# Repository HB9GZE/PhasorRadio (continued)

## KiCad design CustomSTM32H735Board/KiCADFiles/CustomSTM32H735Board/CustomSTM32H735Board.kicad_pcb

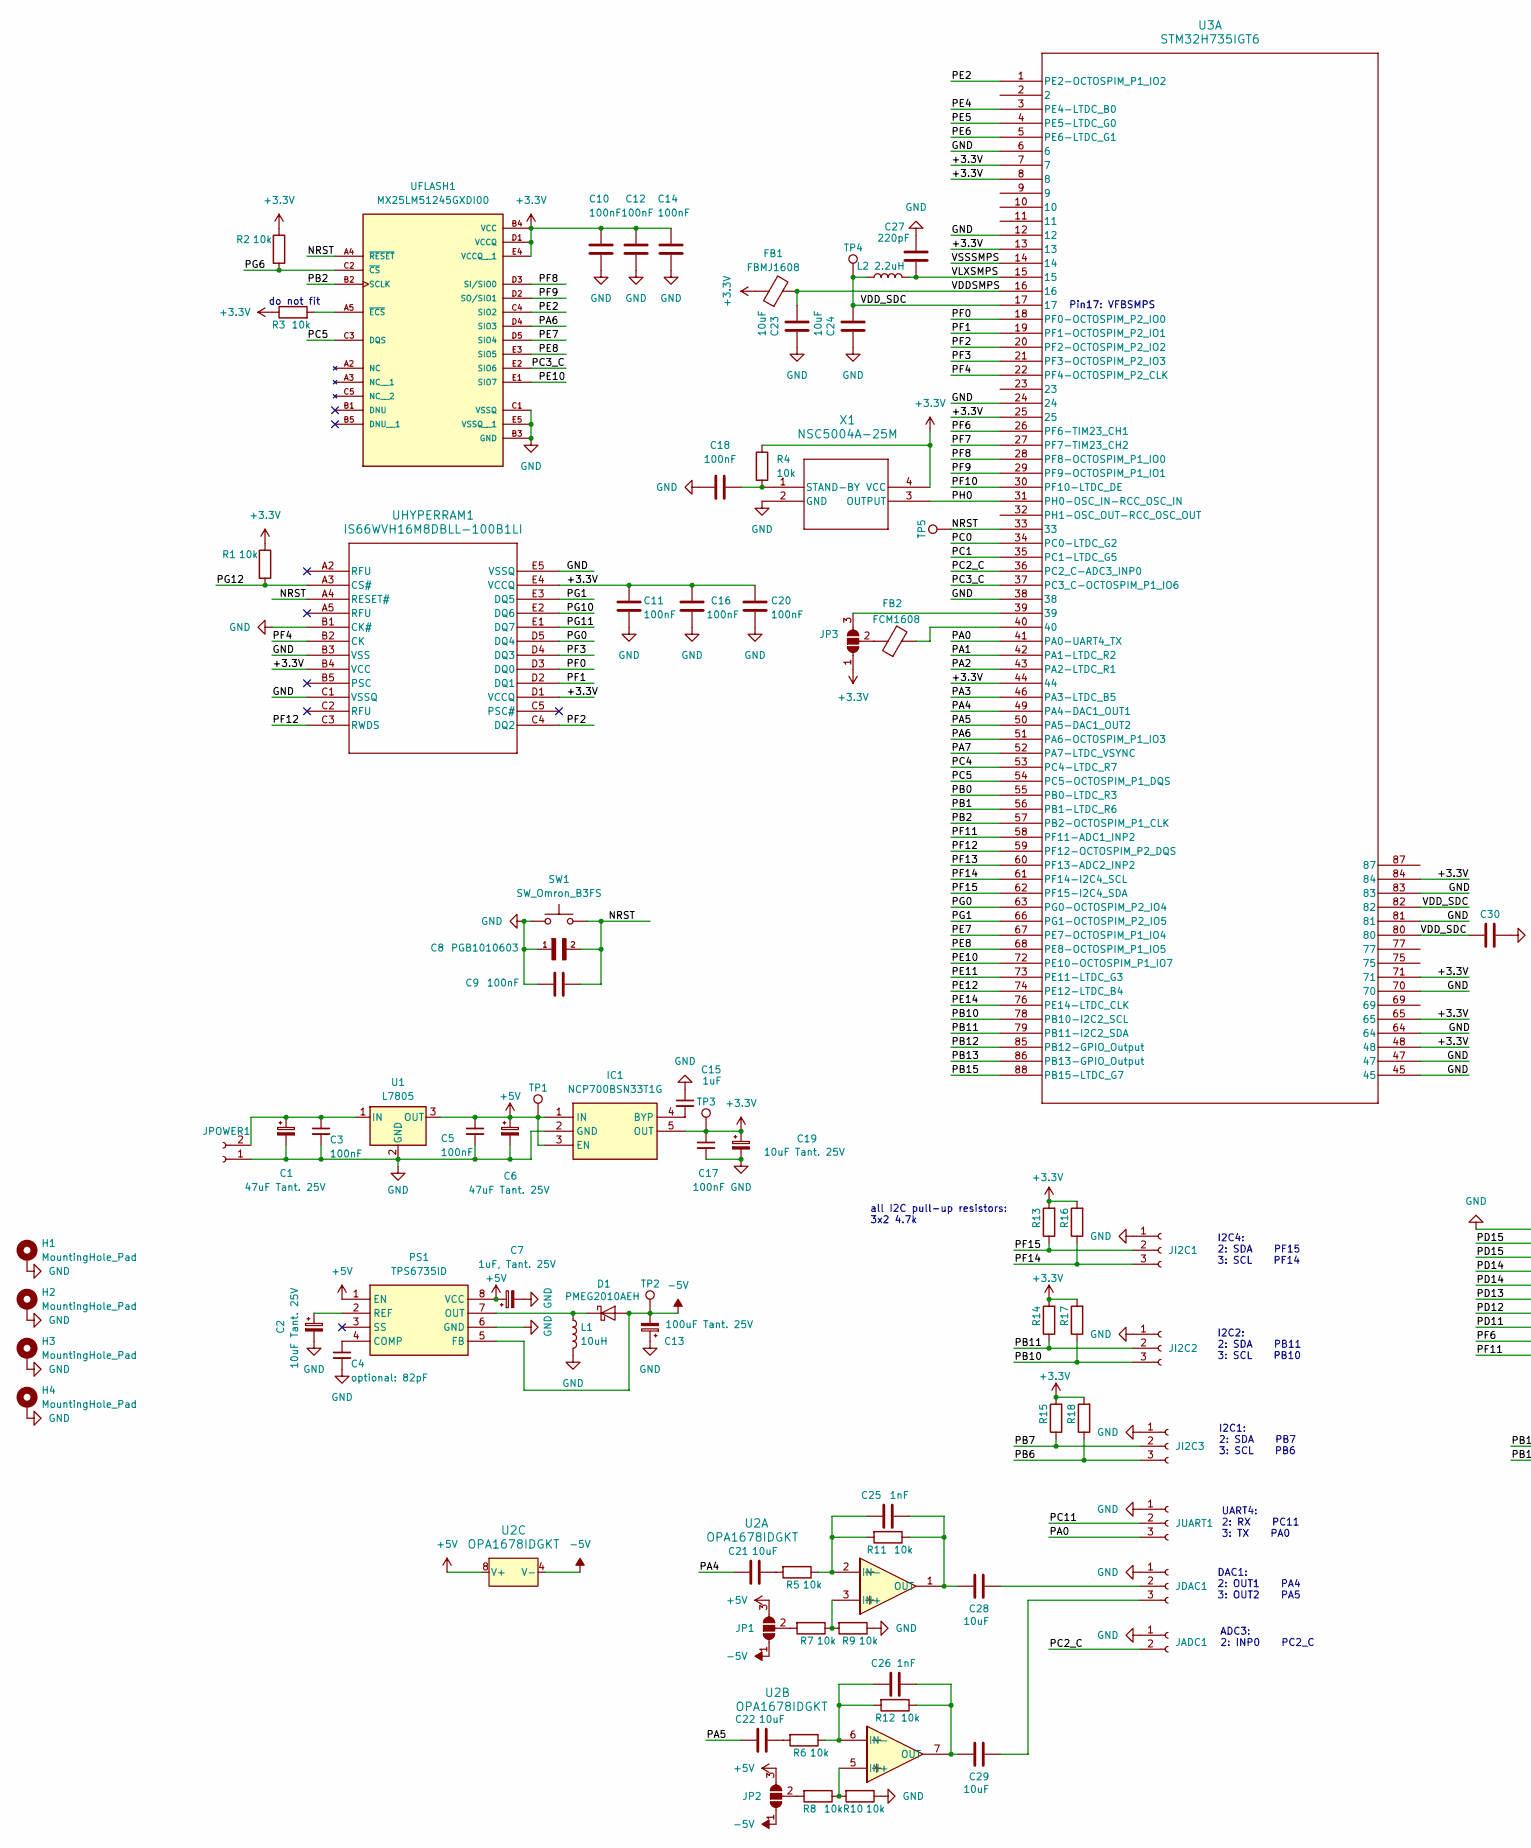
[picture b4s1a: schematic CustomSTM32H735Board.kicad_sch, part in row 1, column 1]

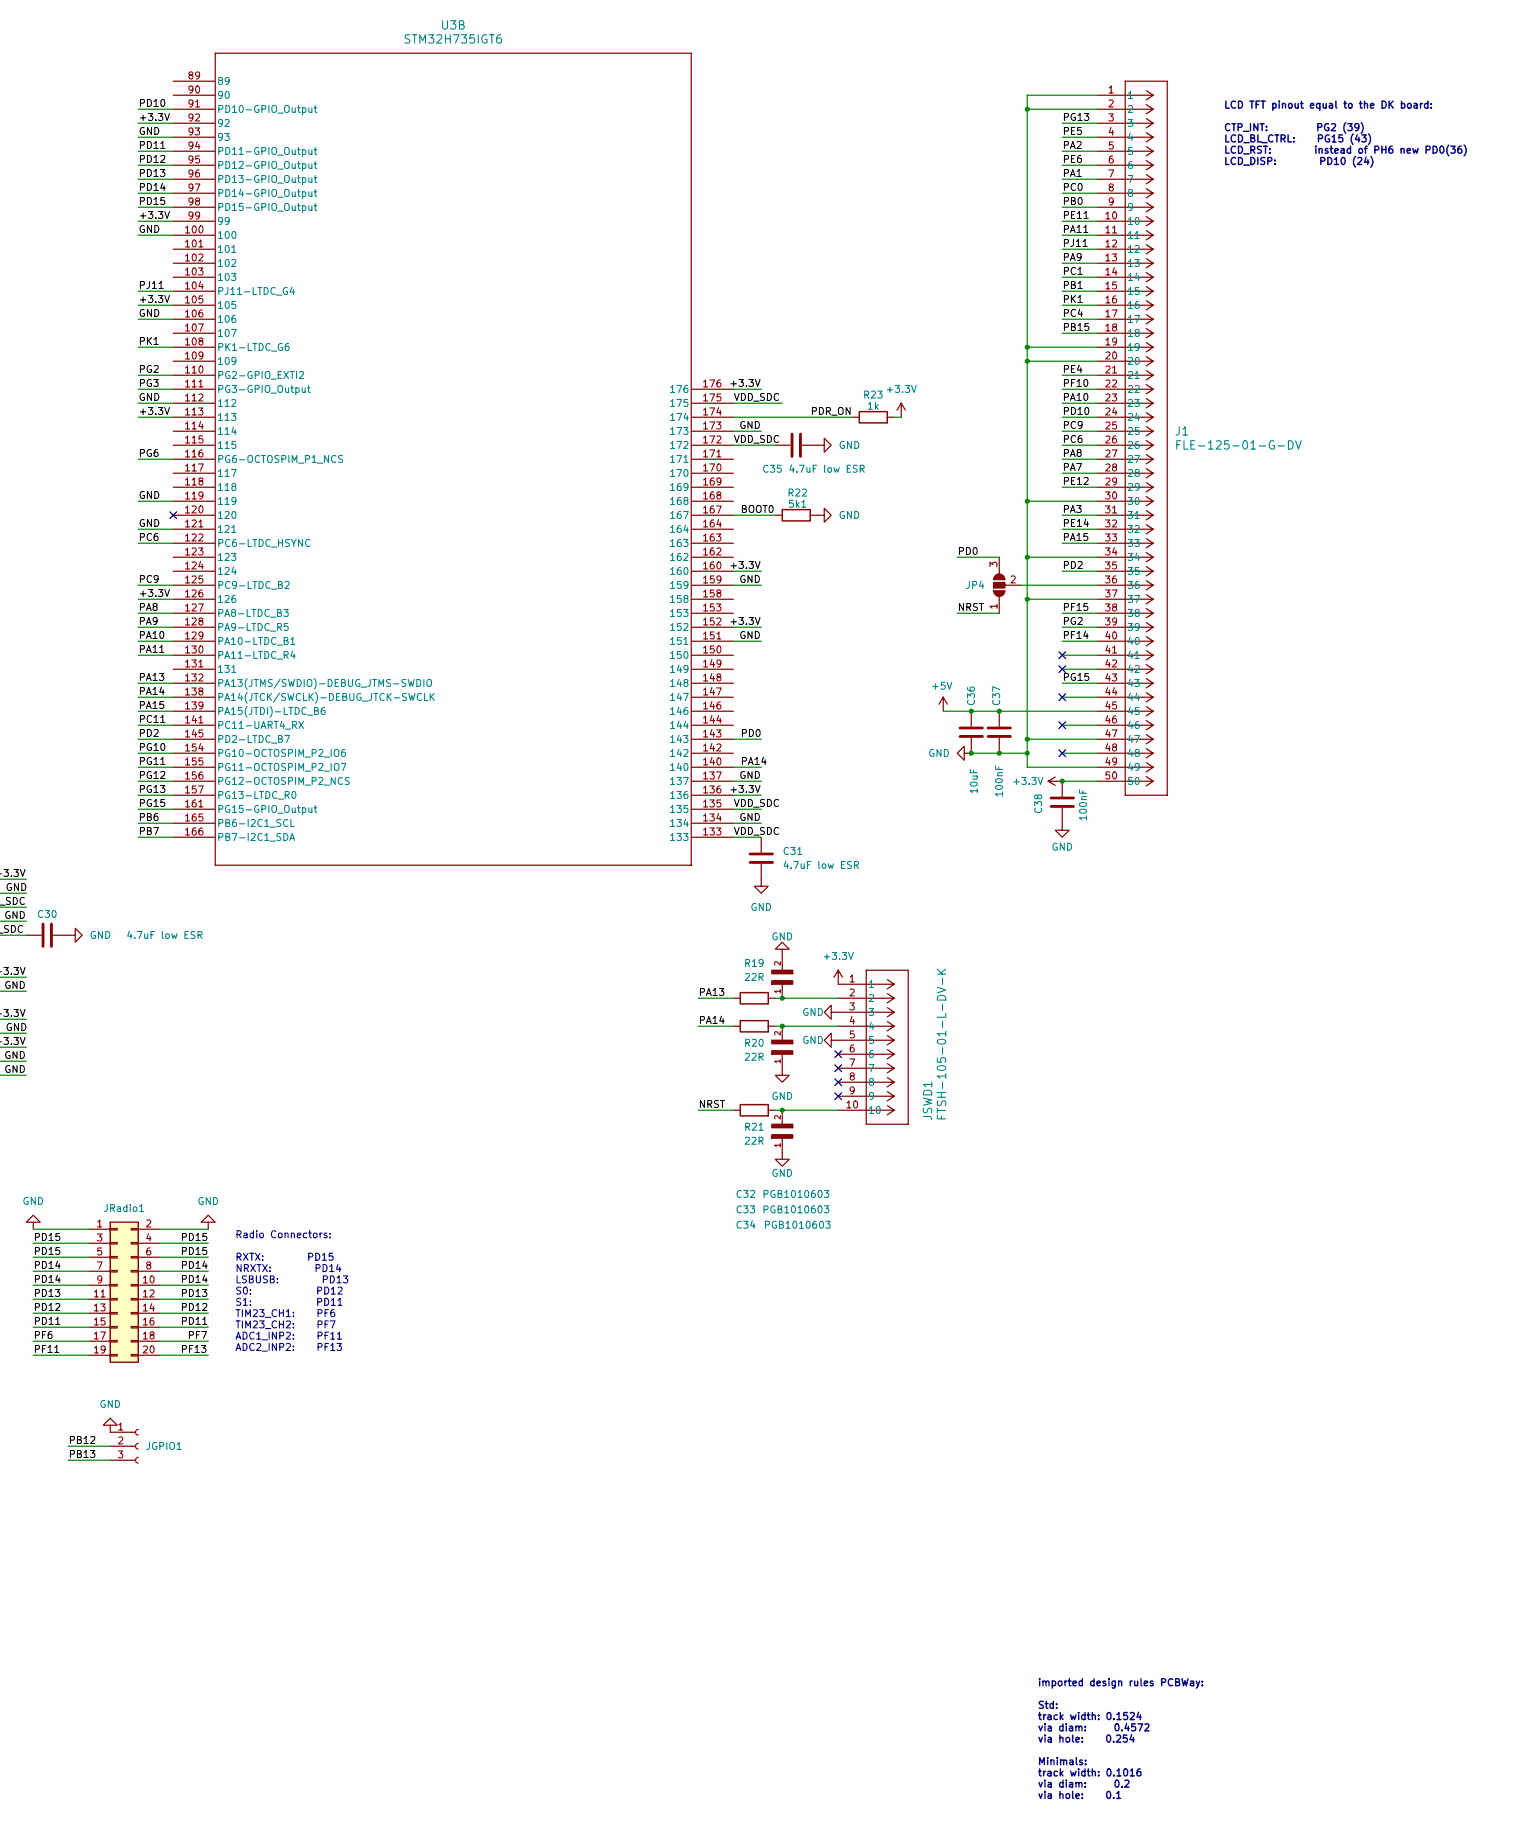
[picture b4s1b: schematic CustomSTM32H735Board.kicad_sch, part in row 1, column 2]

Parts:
C1, C6: 47uF Tant. 25V; CP_EIA-7343-30_AVX-N_Pad2.25x2.55mm_HandSolder
C2, C19: 10uF Tant. 25V; CP_EIA-7343-30_AVX-N_Pad2.25x2.55mm_HandSolder
C3, C5, C9, C10, C11, C12, C14, C16, C17, C18, C20, C37, C38: 100nF; C_0805_2012Metric_Pad1.18x1.45mm_HandSolder
C4: optional: 82pF; C_0805_2012Metric_Pad1.18x1.45mm_HandSolder
C7: 1uF, Tant. 25V; CP_EIA-7343-30_AVX-N_Pad2.25x2.55mm_HandSolder
C8, C32, C33, C34: PGB1010603; C_0603_1608Metric
C13: 100uF Tant. 25V; CP_EIA-7343-30_AVX-N_Pad2.25x2.55mm_HandSolder
C15: 1uF; C_0805_2012Metric_Pad1.18x1.45mm_HandSolder
C21, C22, C23, C24, C28, C29, C36: 10uF; C_0805_2012Metric_Pad1.18x1.45mm_HandSolder
C25, C26: 1nF; C_0805_2012Metric_Pad1.18x1.45mm_HandSolder
C27: 220pF; C_0805_2012Metric_Pad1.18x1.45mm_HandSolder
C30, C31, C35: 4.7uF low ESR; C_0805_2012Metric_Pad1.18x1.45mm_HandSolder
D1: PMEG2010AEH; D_SOD-123F
FB1: FBMJ1608; L_0603_1608Metric_Pad1.05x0.95mm_HandSolder
FB2: FCM1608; L_0603_1608Metric_Pad1.05x0.95mm_HandSolder
H1, H2, H3, H4: MountingHole_Pad; MountingHole_3.2mm_M3_Pad_TopBottom
IC1: NCP700BSN33T1G; SOT95P275X120-5N; Manufacturer_Part_Number NCP700BSN33T1G; Mouser Part Number 863-NCP700BSN33T1G
J1: FLE-125-01-G-DV; CON50_2X25_UF_FLE_SAI
JADC1: Conn_01x02_Socket; JST_XH_B2B-XH-A_1x02_P2.50mm_Vertical
JDAC1: Conn_01x03_Socket; JST_XH_B3B-XH-A_1x03_P2.50mm_Vertical
JGPIO1: Conn_01x03_Socket; JST_XH_B3B-XH-A_1x03_P2.50mm_Vertical
JI2C1, JI2C2, JI2C3: Conn_01x03_Socket; JST_XH_B3B-XH-A_1x03_P2.50mm_Vertical
JP1, JP2, JP3, JP4: SolderJumper_3_Open; SolderJumper-3_P1.3mm_Open_Pad1.0x1.5mm_NumberLabels
JPOWER1: Conn_01x02_Socket; JST_XH_B2B-XH-A_1x02_P2.50mm_Vertical
JRadio1: Conn_02x10_Odd_Even; IDC-Header_2x10_P2.54mm_Vertical
JSWD1: FTSH-105-01-L-DV-K; CON10_2X5_DUK_FTSH_SAI-M
JUART1: Conn_01x03_Socket; JST_XH_B3B-XH-A_1x03_P2.50mm_Vertical
L1: 10uH; L_1812_4532Metric_Pad1.30x3.40mm_HandSolder
L2: 2.2uH; L_Murata_DFE201610P
PS1: TPS6735ID; SOIC127P600X175-8N; Manufacturer_Part_Number TPS6735ID; Mouser Part Number 595-TPS6735ID
R1, R2, R3, R4, R5, R6, R7, R8, R9, R10, R11, R12: 10k; R_0805_2012Metric_Pad1.20x1.40mm_HandSolder
R13, R14, R15, R16, R17, R18: 4.7k; R_0805_2012Metric_Pad1.20x1.40mm_HandSolder
R19, R20, R21: 22R; R_0805_2012Metric_Pad1.20x1.40mm_HandSolder
R22: 5k1; R_0805_2012Metric_Pad1.20x1.40mm_HandSolder
R23: 1k; R_0805_2012Metric_Pad1.20x1.40mm_HandSolder
SW1: SW_Omron_B3FS; SW_SPST_Omron_B3FS-100xP
TP1, TP2, TP3, TP4, TP5: TestPoint; Pin_D0.7mm_L6.5mm_W1.8mm_FlatFork
U1: L7805; TO-220-3_Horizontal_TabDown
U2: OPA1678IDGKT; OPA1678_L
U3: STM32H735IGT6; LQFP176_STM32H735IGT6_STM-M
UFLASH1: MX25LM51245GXDI00; BGA24C100P5X5_600X800X120; PARTREV 1.1
UHYPERRAM1: IS66WVH16M8DBLL-100B1LI; TFBGA24_6X8_ISI
X1: NSC5004A-25M; NSC5004_NDK

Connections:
+3.3V: C10.1, C11.1, C12.1, C14.1, C16.1, C17.1, C19.1, C20.1, C38.1, FB1.1, IC1.5 (OUT), J1.50, JP3.1 (A), JSWD1.1, R1.1, R2.1, R3.1, R4.1, R13.2, R14.2, R15.2, R16.2, R17.2, R18.2, R23.2, TP3.1, U3.7, U3.8, U3.13, U3.25, U3.44, U3.48, U3.65, U3.71, U3.84, U3.92, U3.99, U3.105, U3.113, U3.126, U3.136, U3.152, U3.160, U3.176, UFLASH1.B4 (VCC), UFLASH1.D1 (VCCQ), UFLASH1.E4 (VCCQ__1), UHYPERRAM1.B4 (VCC), UHYPERRAM1.D1 (VCCQ), UHYPERRAM1.E4 (VCCQ), X1.4 (VCC)
+5V: C5.1, C6.1, C7.1, C36.1, C37.1, IC1.1 (IN), IC1.3 (EN), J1.45, JP1.3 (B), JP2.3 (B), PS1.1 (EN), PS1.8 (VCC), TP1.1, U1.3 (OUT), U2.8 (V+)
-5V: C13.2, D1.2 (A), JP1.1 (A), JP2.1 (A), PS1.5 (FB), TP2.1, U2.4 (V-)
/BOOT0: R22.1, U3.167
/NRST: C8.2, C9.1, JP4.1 (A), R21.1, SW1.2, TP5.1, U3.33, UFLASH1.A4 (~RESET), UHYPERRAM1.A4 (RESET#)
/PA0: JUART1.3, U3.41 (PA0-UART4_TX)
/PA1: J1.7, U3.42 (PA1-LTDC_R2)
/PA2: J1.5, U3.43 (PA2-LTDC_R1)
/PA3: J1.31, U3.46 (PA3-LTDC_B5)
/PA4: C21.1, U3.49 (PA4-DAC1_OUT1)
/PA5: C22.1, U3.50 (PA5-DAC1_OUT2)
/PA6: U3.51 (PA6-OCTOSPIM_P1_IO3), UFLASH1.D4 (SIO3)
/PA7: J1.28, U3.52 (PA7-LTDC_VSYNC)
/PA8: J1.27, U3.127 (PA8-LTDC_B3)
/PA9: J1.13, U3.128 (PA9-LTDC_R5)
/PA10: J1.23, U3.129 (PA10-LTDC_B1)
/PA11: J1.11, U3.130 (PA11-LTDC_R4)
/PA13: R19.1, U3.132 (PA13(JTMS/SWDIO)-DEBUG_JTMS-SWDIO)
/PA14: R20.1, U3.138 (PA14(JTCK/SWCLK)-DEBUG_JTCK-SWCLK), U3.140
/PA15: J1.33, U3.139 (PA15(JTDI)-LTDC_B6)
/PB0: J1.9, U3.55 (PB0-LTDC_R3)
/PB1: J1.15, U3.56 (PB1-LTDC_R6)
/PB2: U3.57 (PB2-OCTOSPIM_P1_CLK), UFLASH1.B2 (SCLK)
/PB6: JI2C3.3, R18.1, U3.165 (PB6-I2C1_SCL)
/PB7: JI2C3.2, R15.1, U3.166 (PB7-I2C1_SDA)
/PB10: JI2C2.3, R17.1, U3.78 (PB10-I2C2_SCL)
/PB11: JI2C2.2, R14.1, U3.79 (PB11-I2C2_SDA)
/PB12: JGPIO1.2, U3.85 (PB12-GPIO_Output)
/PB13: JGPIO1.3, U3.86 (PB13-GPIO_Output)
/PB15: J1.18, U3.88 (PB15-LTDC_G7)
/PC0: J1.8, U3.34 (PC0-LTDC_G2)
/PC1: J1.14, U3.35 (PC1-LTDC_G5)
/PC2_C: JADC1.2, U3.36 (PC2_C-ADC3_INP0)
/PC3_C: U3.37 (PC3_C-OCTOSPIM_P1_IO6), UFLASH1.E2 (SIO6)
/PC4: J1.17, U3.53 (PC4-LTDC_R7)
/PC5: U3.54 (PC5-OCTOSPIM_P1_DQS), UFLASH1.C3 (DQS)
/PC6: J1.26, U3.122 (PC6-LTDC_HSYNC)
/PC9: J1.25, U3.125 (PC9-LTDC_B2)
/PC11: JUART1.2, U3.141 (PC11-UART4_RX)
/PD0: JP4.3 (B), U3.143
/PD2: J1.35, U3.145 (PD2-LTDC_B7)
/PD10: J1.24, U3.91 (PD10-GPIO_Output)
/PD11: JRadio1.15, JRadio1.16, U3.94 (PD11-GPIO_Output)
/PD12: JRadio1.13, JRadio1.14, U3.95 (PD12-GPIO_Output)
/PD13: JRadio1.11, JRadio1.12, U3.96 (PD13-GPIO_Output)
/PD14: JRadio1.7, JRadio1.8, JRadio1.9, JRadio1.10, U3.97 (PD14-GPIO_Output)
/PD15: JRadio1.3, JRadio1.4, JRadio1.5, JRadio1.6, U3.98 (PD15-GPIO_Output)
/PDR_ON: R23.1, U3.174
/PE2: U3.1 (PE2-OCTOSPIM_P1_IO2), UFLASH1.C4 (SIO2)
/PE4: J1.21, U3.3 (PE4-LTDC_B0)
/PE5: J1.4, U3.4 (PE5-LTDC_G0)
/PE6: J1.6, U3.5 (PE6-LTDC_G1)
/PE7: U3.67 (PE7-OCTOSPIM_P1_IO4), UFLASH1.D5 (SIO4)
/PE8: U3.68 (PE8-OCTOSPIM_P1_IO5), UFLASH1.E3 (SIO5)
/PE10: U3.72 (PE10-OCTOSPIM_P1_IO7), UFLASH1.E1 (SIO7)
/PE11: J1.10, U3.73 (PE11-LTDC_G3)
/PE12: J1.29, U3.74 (PE12-LTDC_B4)
/PE14: J1.32, U3.76 (PE14-LTDC_CLK)
/PF0: U3.18 (PF0-OCTOSPIM_P2_IO0), UHYPERRAM1.D3 (DQ0)
/PF1: U3.19 (PF1-OCTOSPIM_P2_IO1), UHYPERRAM1.D2 (DQ1)
/PF2: U3.20 (PF2-OCTOSPIM_P2_IO2), UHYPERRAM1.C4 (DQ2)
/PF3: U3.21 (PF3-OCTOSPIM_P2_IO3), UHYPERRAM1.D4 (DQ3)
/PF4: U3.22 (PF4-OCTOSPIM_P2_CLK), UHYPERRAM1.B2 (CK)
/PF6: JRadio1.17, U3.26 (PF6-TIM23_CH1)
/PF7: JRadio1.18, U3.27 (PF7-TIM23_CH2)
/PF8: U3.28 (PF8-OCTOSPIM_P1_IO0), UFLASH1.D3 (SI/SIO0)
/PF9: U3.29 (PF9-OCTOSPIM_P1_IO1), UFLASH1.D2 (SO/SIO1)
/PF10: J1.22, U3.30 (PF10-LTDC_DE)
/PF11: JRadio1.19, U3.58 (PF11-ADC1_INP2)
/PF12: U3.59 (PF12-OCTOSPIM_P2_DQS), UHYPERRAM1.C3 (RWDS)
/PF13: JRadio1.20, U3.60 (PF13-ADC2_INP2)
/PF14: J1.40, JI2C1.3, R16.1, U3.61 (PF14-I2C4_SCL)
/PF15: J1.38, JI2C1.2, R13.1, U3.62 (PF15-I2C4_SDA)
/PG0: U3.63 (PG0-OCTOSPIM_P2_IO4), UHYPERRAM1.D5 (DQ4)
/PG1: U3.66 (PG1-OCTOSPIM_P2_IO5), UHYPERRAM1.E3 (DQ5)
/PG2: J1.39, U3.110 (PG2-GPIO_EXTI2)
/PG3: U3.111 (PG3-GPIO_Output)
/PG6: R2.2, U3.116 (PG6-OCTOSPIM_P1_NCS), UFLASH1.C2 (~CS)
/PG10: U3.154 (PG10-OCTOSPIM_P2_IO6), UHYPERRAM1.E2 (DQ6)
/PG11: U3.155 (PG11-OCTOSPIM_P2_IO7), UHYPERRAM1.E1 (DQ7)
/PG12: R1.2, U3.156 (PG12-OCTOSPIM_P2_NCS), UHYPERRAM1.A3 (CS#)
/PG13: J1.3, U3.157 (PG13-LTDC_R0)
/PG15: J1.43, U3.161 (PG15-GPIO_Output)
/PH0: U3.31 (PH0-OSC_IN-RCC_OSC_IN), X1.3 (OUTPUT)
/PJ11: J1.12, U3.104 (PJ11-LTDC_G4)
/PK1: J1.16, U3.108 (PK1-LTDC_G6)
/VDDSMPS: C23.1, FB1.2, U3.16
/VDD_SDC: C24.1, C30.2, C31.1, C35.2, L2.1, TP4.1, U3.17, U3.80, U3.82, U3.133, U3.135, U3.172, U3.175
/VLXSMPS: C27.2, L2.2, U3.15
unnamed: C21.2, R5.2
unnamed: C22.2, R6.2
unnamed: C32.1, JSWD1.2, R19.2
unnamed: C33.2, JSWD1.4, R20.2
unnamed: C34.2, JSWD1.10, R21.2
unnamed: D1.1 (K), L1.1, PS1.7 (OUT)
unnamed: FB2.2, U3.40
unnamed: C15.2, IC1.4 (BYP)
unnamed: C28.2, JDAC1.2
unnamed: C29.2, JDAC1.3
unnamed: JP1.2 (C), R7.2
unnamed: JP2.2 (C), R8.2
unnamed: JP3.3 (B), U3.39
unnamed: FB2.1, JP3.2 (C)
unnamed: J1.36, JP4.2 (C)
unnamed: C1.1, C3.1, JPOWER1.2, U1.1 (IN)
unnamed: C4.1, PS1.4 (COMP)
unnamed: C2.1, PS1.2 (REF)
unnamed: R7.1, R9.2, U2.3 (IN+)
unnamed: C25.1, R5.1, R11.2, U2.2 (IN-)
unnamed: C25.2, C28.1, R11.1, U2.1 (OUT)
unnamed: R8.1, R10.2, U2.5 (IN+)
unnamed: C26.1, R6.1, R12.2, U2.6 (IN-)
unnamed: C26.2, C29.1, R12.1, U2.7 (OUT)
unnamed: R3.2, UFLASH1.A5 (~ECS)
unnamed: C18.2, R4.2, X1.1 (STAND-BY)

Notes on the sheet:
Pin17: VFBSMPS
DAC1: 2: OUT1 PA4 3: OUT2 PA5
Radio Connectors: RXTX: PD15 NRXTX: PD14 LSBUSB: PD13 S0: PD12 S1: PD11 TIM23_CH1: PF6 TIM23_CH2: PF7 ADC1_INP2: PF11 ADC2_INP2: PF13
LCD TFT pinout equal to the DK board: CTP_INT: PG2 (39) LCD_BL_CTRL: PG15 (43) LCD_RST: instead of PH6 new PD0(36) LCD_DISP: PD10 (24)
I2C1: 2: SDA PB7 3: SCL PB6
do not fit
UART4: 2: RX PC11 3: TX PA0
ADC3: 2: INP0 PC2_C
imported design rules PCBWay: Std: track width: 0.1524 via diam: 0.4572 via hole: 0.254 Minimals: track width: 0.1016 via diam: 0.2 via hole: 0.1
I2C2: 2: SDA PB11 3: SCL PB10
all I2C pull-up resistors: 3x2 4.7k
I2C4: 2: SDA PF15 3: SCL PF14

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
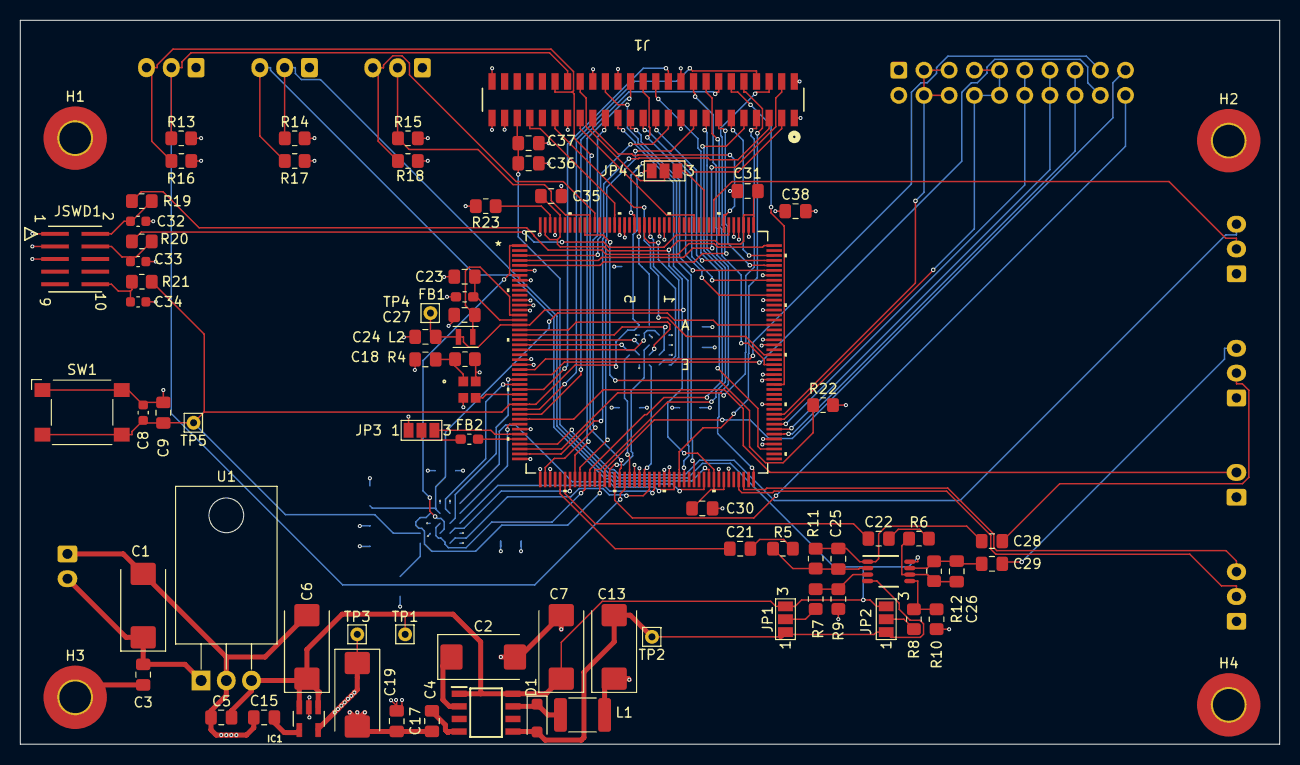
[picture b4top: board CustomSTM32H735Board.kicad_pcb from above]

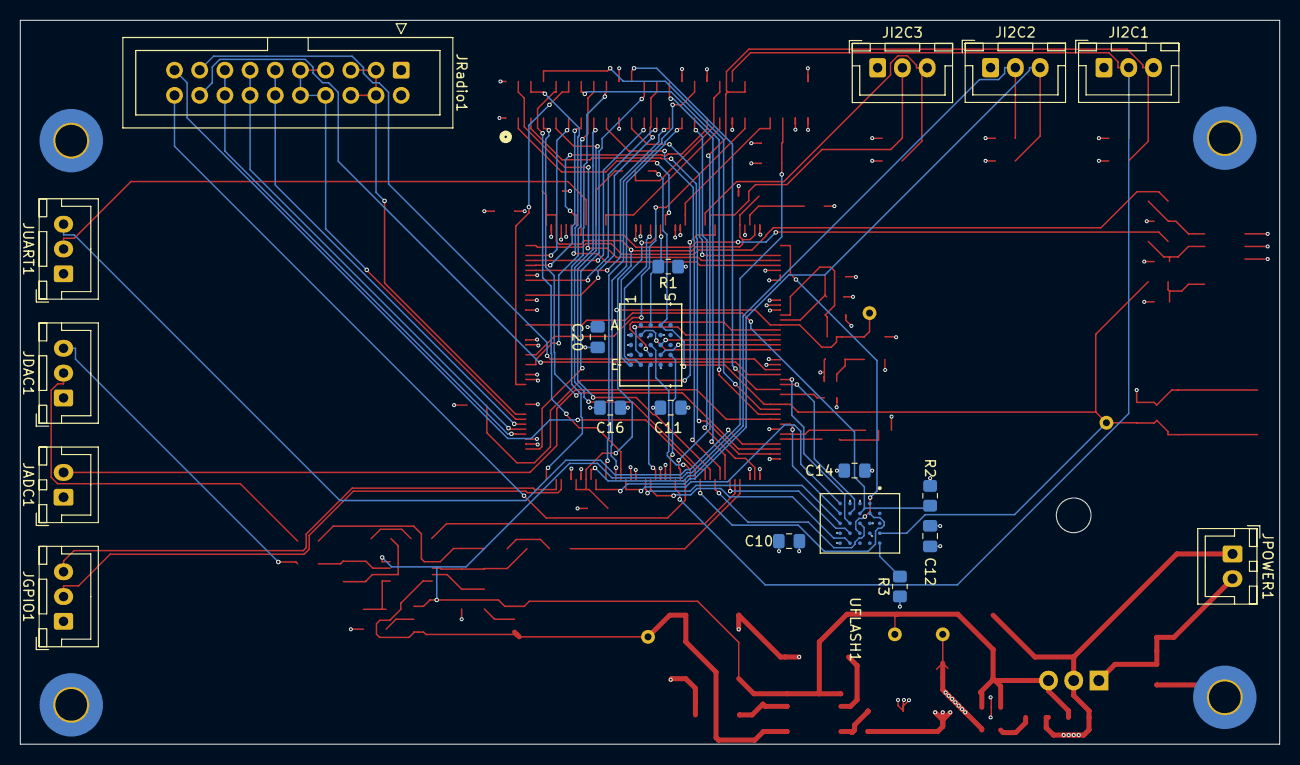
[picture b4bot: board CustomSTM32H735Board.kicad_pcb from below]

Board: 4 copper layers, 127.0 x 73.0 mm, 99 parts (20 on the bottom side), 115 nets.

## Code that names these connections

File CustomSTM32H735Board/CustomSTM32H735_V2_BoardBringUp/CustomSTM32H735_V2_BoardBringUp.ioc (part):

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Mcu.Name=STM32H735IGKx
Mcu.Package=UFBGA176
Mcu.UserName=STM32H735IGKx
PA0.GPIOParameters=GPIO_Speed,GPIO_Label
PA0.GPIO_Label=VSYNC_FREQ
PA0.GPIO_Speed=GPIO_SPEED_FREQ_VERY_HIGH
PA0.Signal=GPIO_Output
PA0_C.Signal=ADCx_INP0
PA12.GPIOParameters=GPIO_Label
PA12.GPIO_Label=LSBUSB
PA12.Signal=GPIO_Output
PA13(JTMS/SWDIO).Mode=Serial_Wire
PA13(JTMS/SWDIO).Signal=DEBUG_JTMS-SWDIO
PA14(JTCK/SWCLK).Mode=Serial_Wire
PA14(JTCK/SWCLK).Signal=DEBUG_JTCK-SWCLK
PA15(JTDI).Signal=S_TIM2_CH1_ETR
PA1_C.Signal=ADCx_INP1
PA3.GPIOParameters=GPIO_Speed
PA3.GPIO_Speed=GPIO_SPEED_FREQ_VERY_HIGH
PA3.Mode=RGB888
PA3.Signal=LTDC_B5
PA4.GPIOParameters=GPIO_Speed
PA4.GPIO_Speed=GPIO_SPEED_FREQ_VERY_HIGH
PA4.Mode=RGB888
PA4.Signal=LTDC_VSYNC
PA5.Signal=COMP_DAC12_group
PA6.GPIOParameters=GPIO_Speed
PA6.GPIO_Speed=GPIO_SPEED_FREQ_VERY_HIGH
PA6.Mode=RGB888
PA6.Signal=LTDC_G2
PA8.GPIOParameters=GPIO_Speed
PA8.GPIO_Speed=GPIO_SPEED_FREQ_VERY_HIGH
PA8.Mode=RGB888
PA8.Signal=LTDC_B3
PB0.GPIOParameters=GPIO_Speed
PB0.GPIO_Speed=GPIO_SPEED_FREQ_VERY_HIGH
PB0.Mode=RGB888
PB0.Signal=LTDC_G1
PB1.GPIOParameters=GPIO_Speed
PB1.GPIO_Speed=GPIO_SPEED_FREQ_VERY_HIGH
PB1.Mode=RGB888
PB1.Signal=LTDC_G0
PB10.Mode=I2C
PB10.Signal=I2C2_SCL
PB11.Mode=I2C
PB11.Signal=I2C2_SDA
PB12.GPIOParameters=GPIO_Label
PB12.GPIO_Label=S0
PB12.Signal=GPIO_Output
PB13.GPIOParameters=GPIO_Label
PB13.GPIO_Label=S1
PB13.Signal=GPIO_Output
PB14.GPIOParameters=GPIO_Speed,GPIO_Label
PB14.GPIO_Label=FRAME_RATE
PB14.GPIO_Speed=GPIO_SPEED_FREQ_VERY_HIGH
PB14.Signal=GPIO_Output
PB15.GPIOParameters=GPIO_Speed,GPIO_Label
PB15.GPIO_Label=MCU_ACTIVE
PB15.GPIO_Speed=GPIO_SPEED_FREQ_VERY_HIGH
PB15.Signal=GPIO_Output
PB2.Mode=OCTOSPI1_Port1_DQS
PB2.Signal=OCTOSPIM_P1_DQS
PB3(JTDO/TRACESWO).Signal=S_TIM2_CH2
PB8.GPIOParameters=GPIO_Speed
PB8.GPIO_Speed=GPIO_SPEED_FREQ_VERY_HIGH
PB8.Mode=RGB888
PB8.Signal=LTDC_B6
PB9.GPIOParameters=GPIO_Speed
PB9.GPIO_Speed=GPIO_SPEED_FREQ_VERY_HIGH
PB9.Mode=RGB888
PB9.Signal=LTDC_B7
PC2_C.Mode=IN0-Single-Ended
PC2_C.Signal=ADC3_INP0
PC4.Mode=Follower-DAC_OUT1-INP
PC4.Signal=OPAMP1_VOUT
PC6.GPIOParameters=GPIO_Speed
PC6.GPIO_Speed=GPIO_SPEED_FREQ_VERY_HIGH
PC6.Mode=RGB888
PC6.Signal=LTDC_HSYNC
PC7.GPIOParameters=GPIO_Speed
PC7.GPIO_Speed=GPIO_SPEED_FREQ_VERY_HIGH
PC7.Mode=RGB888
PC7.Signal=LTDC_G6
PC9.Mode=I2C
PC9.Signal=I2C3_SDA
PD0.GPIOParameters=GPIO_Speed
PD0.GPIO_Speed=GPIO_SPEED_FREQ_VERY_HIGH
PD0.Mode=RGB888
PD0.Signal=LTDC_B1
PD1.Mode=Asynchronous
PD1.Signal=UART4_TX
PD10.GPIOParameters=GPIO_Speed,PinState,GPIO_PuPd,GPIO_Label
PD10.GPIO_Label=LCD_DISP
PD10.GPIO_PuPd=GPIO_NOPULL
PD10.GPIO_Speed=GPIO_SPEED_FREQ_LOW
PD10.PinState=GPIO_PIN_RESET
PD10.Signal=GPIO_Output
PD11.Mode=OCTOSPI1_IOL_Port1L
PD11.Signal=OCTOSPIM_P1_IO0
PD12.Mode=OCTOSPI1_IOL_Port1L
PD12.Signal=OCTOSPIM_P1_IO1
PD13.Mode=OCTOSPI1_IOL_Port1L
PD13.Signal=OCTOSPIM_P1_IO3
PD3.GPIOParameters=GPIO_Speed
PD3.GPIO_Speed=GPIO_SPEED_FREQ_VERY_HIGH
PD3.Mode=RGB888
PD3.Signal=LTDC_G7
PD4.Mode=OCTOSPI1_IOH_Port1H
PD4.Signal=OCTOSPIM_P1_IO4
PD5.Mode=OCTOSPI1_IOH_Port1H
PD5.Signal=OCTOSPIM_P1_IO5
PD6.GPIOParameters=GPIO_Speed
PD6.GPIO_Speed=GPIO_SPEED_FREQ_VERY_HIGH
PD6.Mode=RGB888
PD6.Signal=LTDC_B2
PD7.Mode=OCTOSPI1_IOH_Port1H
PD7.Signal=OCTOSPIM_P1_IO7
PE0.GPIOParameters=GPIO_Speed
PE0.GPIO_Speed=GPIO_SPEED_FREQ_VERY_HIGH
PE0.Mode=RGB888
PE0.Signal=LTDC_R0
PE1.GPIOParameters=GPIO_Speed
PE1.GPIO_Speed=GPIO_SPEED_FREQ_VERY_HIGH
PE1.Mode=RGB888
PE1.Signal=LTDC_R6
PE11.GPIOParameters=GPIO_Speed
PE11.GPIO_Speed=GPIO_SPEED_FREQ_VERY_HIGH
PE11.Mode=RGB888
PE11.Signal=LTDC_G3
PE12.GPIOParameters=GPIO_Speed
PE12.GPIO_Speed=GPIO_SPEED_FREQ_VERY_HIGH
PE12.Mode=RGB888
PE12.Signal=LTDC_B4
PE13.GPIOParameters=GPIO_Speed
PE13.GPIO_Speed=GPIO_SPEED_FREQ_VERY_HIGH
PE13.Mode=RGB888
PE13.Signal=LTDC_DE
PE15.GPIOParameters=GPIO_Speed
PE15.GPIO_Speed=GPIO_SPEED_FREQ_VERY_HIGH
PE15.Mode=RGB888
PE15.Signal=LTDC_R7
PE2.Mode=OCTOSPI1_IOL_Port1L
PE2.Signal=OCTOSPIM_P1_IO2
PE4.GPIOParameters=GPIO_Label
PE4.GPIO_Label=GPIO_PE4
PE4.Signal=GPIO_Output
PF0.Mode=OCTOSPI2_IOL_Port2L
PF0.Signal=OCTOSPIM_P2_IO0
PF1.Mode=OCTOSPI2_IOL_Port2L
PF1.Signal=OCTOSPIM_P2_IO1
PF10.Mode=O1_P1_CLK
PF10.Signal=OCTOSPIM_P1_CLK
PF12.Mode=OCTOSPI2_Port2_DQS
PF12.Signal=OCTOSPIM_P2_DQS
PF14.Mode=I2C
PF14.Signal=I2C4_SCL
PF15.Mode=I2C
PF15.Signal=I2C4_SDA
PF2.Mode=OCTOSPI2_IOL_Port2L
PF2.Signal=OCTOSPIM_P2_IO2
PF3.Mode=OCTOSPI2_IOL_Port2L
PF3.Signal=OCTOSPIM_P2_IO3
PF4.Mode=O2_P2_CLK
PF4.Signal=OCTOSPIM_P2_CLK
PF6.Mode=Encoder_Interface
PF6.Signal=TIM23_CH1
PG0.Mode=OCTOSPI2_IOH_Port2H
PG0.Signal=OCTOSPIM_P2_IO4
PG1.Mode=OCTOSPI2_IOH_Port2H
PG1.Signal=OCTOSPIM_P2_IO5
PG10.Mode=OCTOSPI2_IOH_Port2H
PG10.Signal=OCTOSPIM_P2_IO6
PG11.Mode=OCTOSPI2_IOH_Port2H
PG11.Signal=OCTOSPIM_P2_IO7
PG12.Mode=OCTOSPI2_Port2_NCS
PG12.Signal=OCTOSPIM_P2_NCS
PG13.Signal=S_TIM23_CH2
PG14.GPIOParameters=GPIO_Speed
PG14.GPIO_Speed=GPIO_SPEED_FREQ_VERY_HIGH
PG14.Mode=RGB888
PG14.Signal=LTDC_B0
PG15.GPIOParameters=GPIO_Label
PG15.GPIO_Label=LCD_BL_CTRL
PG15.Signal=GPIO_Output
PG2.GPIOParameters=GPIO_Label
PG2.GPIO_Label=CTP_INT
PG2.Signal=GPXTI2
PG3.GPIOParameters=GPIO_Speed,GPIO_Label
PG3.GPIO_Label=RENDER_TIME
PG3.GPIO_Speed=GPIO_SPEED_FREQ_VERY_HIGH
PG3.Signal=GPIO_Output
PG5.GPIOParameters=GPIO_Label
PG5.GPIO_Label=RXTX
PG5.Signal=GPIO_Output
PG6.Mode=OCTOSPI1_Port1_NCS
PG6.Signal=OCTOSPIM_P1_NCS
PG7.GPIOParameters=GPIO_Speed
PG7.GPIO_Speed=GPIO_SPEED_FREQ_VERY_HIGH
PG7.Mode=RGB888
PG7.Signal=LTDC_CLK
PG9.Mode=OCTOSPI1_IOH_Port1H
PG9.Signal=OCTOSPIM_P1_IO6
PH0-OSC_IN.Mode=HSE-External-Oscillator
PH0-OSC_IN.Signal=RCC_OSC_IN
PH1-OSC_OUT.Mode=HSE-External-Oscillator
PH1-OSC_OUT.Signal=RCC_OSC_OUT
PH10.GPIOParameters=GPIO_Speed
PH10.GPIO_Speed=GPIO_SPEED_FREQ_VERY_HIGH
PH10.Mode=RGB888
PH10.Signal=LTDC_R4
PH11.GPIOParameters=GPIO_Speed
PH11.GPIO_Speed=GPIO_SPEED_FREQ_VERY_HIGH
PH11.Mode=RGB888
PH11.Signal=LTDC_R5
PH12.GPIOParameters=GPIO_Label
PH12.GPIO_Label=NRXTX
PH12.Signal=GPIO_Output
PH14.Mode=Asynchronous
PH14.Signal=UART4_RX
PH15.GPIOParameters=GPIO_Speed
PH15.GPIO_Speed=GPIO_SPEED_FREQ_VERY_HIGH
PH15.Mode=RGB888
PH15.Signal=LTDC_G4
PH3.GPIOParameters=GPIO_Speed
PH3.GPIO_Speed=GPIO_SPEED_FREQ_VERY_HIGH
PH3.Mode=RGB888
PH3.Signal=LTDC_R1
PH4.GPIOParameters=GPIO_Speed
PH4.GPIO_Speed=GPIO_SPEED_FREQ_VERY_HIGH
PH4.Mode=RGB888
PH4.Signal=LTDC_G5
PH6.GPIOParameters=GPIO_Label
PH6.GPIO_Label=LCD_RST
PH6.Signal=GPIO_Output
PH7.Mode=I2C
PH7.Signal=I2C3_SCL
PH8.GPIOParameters=GPIO_Speed
PH8.GPIO_Speed=GPIO_SPEED_FREQ_VERY_HIGH
PH8.Mode=RGB888
PH8.Signal=LTDC_R2
PH9.GPIOParameters=GPIO_Speed
PH9.GPIO_Speed=GPIO_SPEED_FREQ_VERY_HIGH
PH9.Mode=RGB888
PH9.Signal=LTDC_R3
RCC.SYSCLKFreq_VALUE=275000000
RCC.SYSCLKSource=RCC_SYSCLKSOURCE_PLLCLK
board=custom

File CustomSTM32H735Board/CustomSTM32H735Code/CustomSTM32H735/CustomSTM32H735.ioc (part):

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Mcu.Name=STM32H735IGTx
Mcu.Package=LQFP176
Mcu.UserName=STM32H735IGTx
PA0.Mode=Asynchronous
PA0.Signal=UART4_TX
PA1.Mode=RGB888
PA1.Signal=LTDC_R2
PA10.Mode=RGB888
PA10.Signal=LTDC_B1
PA11.Mode=RGB888
PA11.Signal=LTDC_R4
PA13(JTMS/SWDIO).Mode=Serial_Wire
PA13(JTMS/SWDIO).Signal=DEBUG_JTMS-SWDIO
PA14(JTCK/SWCLK).Mode=Serial_Wire
PA14(JTCK/SWCLK).Signal=DEBUG_JTCK-SWCLK
PA15(JTDI).Mode=RGB888
PA15(JTDI).Signal=LTDC_B6
PA2.Mode=RGB888
PA2.Signal=LTDC_R1
PA3.Mode=RGB888
PA3.Signal=LTDC_B5
PA4.Signal=COMP_DAC11_group
PA5.Signal=COMP_DAC12_group
PA6.Mode=OCTOSPI1_IOL_Port1L
PA6.Signal=OCTOSPIM_P1_IO3
PA7.Mode=RGB888
PA7.Signal=LTDC_VSYNC
PA8.Mode=RGB888
PA8.Signal=LTDC_B3
PA9.Mode=RGB888
PA9.Signal=LTDC_R5
PB0.Mode=RGB888
PB0.Signal=LTDC_R3
PB1.Mode=RGB888
PB1.Signal=LTDC_R6
PB10.Mode=I2C
PB10.Signal=I2C2_SCL
PB11.Mode=I2C
PB11.Signal=I2C2_SDA
PB12.Signal=GPIO_Output
PB13.Signal=GPIO_Output
PB15.Mode=RGB888
PB15.Signal=LTDC_G7
PB2.Mode=O1_P1_CLK
PB2.Signal=OCTOSPIM_P1_CLK
PB6.Mode=I2C
PB6.Signal=I2C1_SCL
PB7.Mode=I2C
PB7.Signal=I2C1_SDA
PC0.Mode=RGB888
PC0.Signal=LTDC_G2
PC1.Mode=RGB888
PC1.Signal=LTDC_G5
PC11.Mode=Asynchronous
PC11.Signal=UART4_RX
PC2_C.Mode=IN0-Single-Ended
PC2_C.Signal=ADC3_INP0
PC3_C.Mode=OCTOSPI1_IOH_Port1H
PC3_C.Signal=OCTOSPIM_P1_IO6
PC4.Mode=RGB888
PC4.Signal=LTDC_R7
PC5.Mode=OCTOSPI1_Port1_DQS
PC5.Signal=OCTOSPIM_P1_DQS
PC6.Mode=RGB888
PC6.Signal=LTDC_HSYNC
PC9.Mode=RGB888
PC9.Signal=LTDC_B2
PD0.Signal=GPIO_Output
PD10.Signal=GPIO_Output
PD11.Signal=GPIO_Output
PD12.Signal=GPIO_Output
PD13.Signal=GPIO_Output
PD14.Signal=GPIO_Output
PD15.Signal=GPIO_Output
PD2.Mode=RGB888
PD2.Signal=LTDC_B7
PE10.Mode=OCTOSPI1_IOH_Port1H
PE10.Signal=OCTOSPIM_P1_IO7
PE11.Mode=RGB888
PE11.Signal=LTDC_G3
PE12.Mode=RGB888
PE12.Signal=LTDC_B4
PE14.Mode=RGB888
PE14.Signal=LTDC_CLK
PE2.Mode=OCTOSPI1_IOL_Port1L
PE2.Signal=OCTOSPIM_P1_IO2
PE4.Mode=RGB888
PE4.Signal=LTDC_B0
PE5.Mode=RGB888
PE5.Signal=LTDC_G0
PE6.Mode=RGB888
PE6.Signal=LTDC_G1
PE7.Mode=OCTOSPI1_IOH_Port1H
PE7.Signal=OCTOSPIM_P1_IO4
PE8.Mode=OCTOSPI1_IOH_Port1H
PE8.Signal=OCTOSPIM_P1_IO5
PF0.Mode=OCTOSPI2_IOL_Port2L
PF0.Signal=OCTOSPIM_P2_IO0
PF1.Mode=OCTOSPI2_IOL_Port2L
PF1.Signal=OCTOSPIM_P2_IO1
PF10.Mode=RGB888
PF10.Signal=LTDC_DE
PF11.Mode=IN2-Single-Ended
PF11.Signal=ADC1_INP2
PF12.Mode=OCTOSPI2_Port2_DQS
PF12.Signal=OCTOSPIM_P2_DQS
PF13.Mode=IN2-Single-Ended
PF13.Signal=ADC2_INP2
PF14.Mode=I2C
PF14.Signal=I2C4_SCL
PF15.Mode=I2C
PF15.Signal=I2C4_SDA
PF2.Mode=OCTOSPI2_IOL_Port2L
PF2.Signal=OCTOSPIM_P2_IO2
PF3.Mode=OCTOSPI2_IOL_Port2L
PF3.Signal=OCTOSPIM_P2_IO3
PF4.Mode=O2_P2_CLK
PF4.Signal=OCTOSPIM_P2_CLK
PF6.Mode=Encoder_Interface
PF6.Signal=TIM23_CH1
PF7.Signal=S_TIM23_CH2
PF8.Mode=OCTOSPI1_IOL_Port1L
PF8.Signal=OCTOSPIM_P1_IO0
PF9.Mode=OCTOSPI1_IOL_Port1L
PF9.Signal=OCTOSPIM_P1_IO1
PG0.Mode=OCTOSPI2_IOH_Port2H
PG0.Signal=OCTOSPIM_P2_IO4
PG1.Mode=OCTOSPI2_IOH_Port2H
PG1.Signal=OCTOSPIM_P2_IO5
PG10.Mode=OCTOSPI2_IOH_Port2H
PG10.Signal=OCTOSPIM_P2_IO6
PG11.Mode=OCTOSPI2_IOH_Port2H
PG11.Signal=OCTOSPIM_P2_IO7
PG12.Mode=OCTOSPI2_Port2_NCS
PG12.Signal=OCTOSPIM_P2_NCS
PG13.Mode=RGB888
PG13.Signal=LTDC_R0
PG15.Signal=GPIO_Output
PG2.Signal=GPXTI2
PG6.Mode=OCTOSPI1_Port1_NCS
PG6.Signal=OCTOSPIM_P1_NCS
PH0-OSC_IN.Mode=HSE-External-Oscillator
PH0-OSC_IN.Signal=RCC_OSC_IN
PH1-OSC_OUT.Mode=HSE-External-Oscillator
PH1-OSC_OUT.Signal=RCC_OSC_OUT
PJ11.Mode=RGB888
PJ11.Signal=LTDC_G4
PK1.Mode=RGB888
PK1.Signal=LTDC_G6
RCC.SYSCLKFreq_VALUE=550000000
RCC.SYSCLKSource=RCC_SYSCLKSOURCE_PLLCLK
board=custom

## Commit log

2024-05-30 Initial Commit
    This ist the initial commit from the coder PC
2024-05-30 added one office file for test
2024-05-30 added PowerAmpDesign files
2024-05-30 deleted test file again
2024-05-30 tried to eliminate the PLL reset and the popping noise
    Seems not to work. To get a defined phase shift between the outputs, one need this PLL resets.
    Better way: just generate one output signal and generate the quadrature signal by HW.
2024-05-31 added Git Shortcut
2024-05-31 experiments with Si5351 to prove, that one channel operation does not need a PLL reset for frequency update
2024-05-31 from Office PC
2024-05-31 added custom CPU board design to this resporitory
2024-05-31 Added Cube MX configuration for custom board
    Also deleted the unused i2c4 mutex
2024-06-02 added sMeterValue erived from magnitude mag_f32 array. Added in screen1 the selected WFBW as text
2024-06-02 Spectrum display calibrated
2024-06-05 started to assign LCD connector to STM32H735. Added NRST and Boot0 switch.
2024-06-06 added VSS and VDD on custom board layout
2024-06-06 some .ioc changes only
2024-06-06 Added SWD pinout to custom board
2024-06-08 cleaned up repo by eliminating double STM32-DK files
2024-06-08 minor eclipse stuff (need to set up .itignore I know...
2024-06-09 Work on layout and PCB of custom board. All connectors added. PCB size first draft.
2024-06-09 monir clean up (closing files)
2024-06-09 added in MX more periferals (ADC3 and made shure, that LCD uses same ports as in DK board)
2024-06-10 add in MX the GPIO for the radio basic function RXTX, LSBUSB, and so on.
2024-06-10 added some GPIO for radio functionality
2024-06-10 more work on schematics
2024-06-10 new STM32H7 symbol added for custom board
2024-06-10 some KiCAD meta data only, grrrr
2024-06-10 metadata only
2024-06-10 more schematic work done: DAC output
2024-06-10 more KiCAD work performed
2024-06-11 finished schematics, check with AS performed
2024-06-12 Layout finished. Started with board design of custom board.
2024-06-13 removeg GPIO PG3 because not used
2024-06-13 work on layout, first possible solution
2024-06-14 finished PCB and ordered at AISLER
2024-08-13 lots of custom board bring up stuff
2024-08-13 more custom borad bring up stuff
2024-08-13 V2 Board added
2024-08-14 custom board V2 start
2024-08-14 created new KiCAD files for V2 board (save as)
2024-08-14 KiCAD V2 board progress
2024-08-15 minor
2024-08-15 TIM23 added
2024-08-15 new CAD model
2024-08-15 local changes?
2024-08-16 board schematics V2 checked and final
2024-08-22 Final 6 Layer Board
2024-08-26 finished v2.1 and send off to JLCPCB
2024-09-21 update only
2024-11-03 stuff that I can not remember
2024-11-03 stuff from older times before summer 2024
2024-11-06 old code updated for new custom hardware. Second I2C added just for Si5351.
2024-11-06 player arround with i2c3 speed. Stayed at 100kHz. But maybe a Si5151 Task would be nice to delay the Si5351 update a bit.
2024-11-07 added 74AC74 at mixer board
2024-11-07 some code updates...
2024-11-08 tweeking the SDC conversion...
2024-11-09 minior KiCAD Mixer
2024-11-10 after ADC repair
2024-11-11 fixed bandswitch "snedDatoToSI5351" was missing
2024-11-11 more work on new Mixer
2024-11-11 added ti mixer board
2024-11-13 added SI5351 update task
2024-11-20 started digital filter messed around with Si5351 together with 74AC74
2024-11-21 started design mixer2 with Si5351 on board
2024-11-22 final mixer2 board
2024-11-26 minor minor stuff
2024-11-28 some code adaption to new Si5351 operationg regime (only one channel)
2024-11-28 new comment to use simple Si5351 _Calc next time
2024-12-01 Very fianl Version 1.0 working well
2024-12-02 ready to implement FIR filter
2024-12-03 FIR filter implemented
2024-12-06 implemented UART for scope debug
2024-12-06 FabLab Experiments
2024-12-08 more UART debugging
2024-12-08 I dont know anymore
2024-12-08 what the heck
2024-12-08 small stuff trying to get it working...
2024-12-08 Revert "small stuff trying to get it working..."
    This reverts commit 2b531a6d41b7d2bb143d7d4f776eb645b0272f6b.
    # Conflicts:
    # workspace/.metadata/.ide.log
    # workspace/.metadata/.log
    # workspace/.metadata/.plugins/org.eclipse.cdt.core/.log
    # workspace/.metadata/.plugins/org.eclipse.cdt.core/STM32H735G-DK.1730815950425.pdom
2024-12-08 lost
